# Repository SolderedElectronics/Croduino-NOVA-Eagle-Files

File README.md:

# Croduino NOVA Open Source Hardware Files

Buy Croduino NOVA [here](https://e-radionica.com/en/croduino-nova.html).

## Description and details
Croduino NOVA is microcontroller board capable of connecting to WiFi Internet network, made in Croatia(EU). It is based on very popular ESP8266 which is struggle to use standalone. With NOVA, just plug the board into USB port and start programming your next Internet-connected project(IoT)! Besides that, the board fits perfectly into a breadboard so prototyping is even more simple. Connecting the physical world to internet was never easier.

The braing of NOVA is ESP8266 produced by Espressif. It comes with complete WiFi(client and server side) and integrated TCP/IP stack which supports DNS. The most important thing - it is programmable from Arduino, there is even no need to manually reset the board due to auto-reset circuit onboard. It works at 80MHz frequency, has 1MB of flash for your code(of which 0.8MB available to you) and 82kB of RAM memory(of which 49kB available to you). NOVA also supports I2C, SPI and serial communication, there is 9 GPIO for you of which all support PWM and 1 analog input. Additionally, there is onboard: CP2102 USB to UART bridge (used for USB communication), 3.3V voltage regulator, 4 LEDs, it has FCC and CE certificate etc. In detail:

- ESP8266 in ESP-12 package
- 80MHz, 1MB flash, 82kB RAM
- programmable from Arduina!
- 9 GPIO pins of which all support PWM
- 1 analog input(ADC), max. voltage 1V i 5V
- I2C, SPI, serial communication
- CP2102 USB to UART bridge with micro USB connector
- 3.3V voltage regulator
- LEDs: power, tx, rx, GPIO13
- automatical hardware reset before upload of code
- two pushbuttons: reset i GPIO0
- comes with micro USB cable
- FCC i CE certificates for ESP-12

ESP8266 on-board is loaded with default bootloader.

## Repository content
This repo contains Cadsoft Eagle .sch and .brd files for the board. It also contains schematic in .pdf created from .sch Eagle file. 
Files have been arranged into folders for navigating between different versions of board. 
Tip: layer 200 shows top silkscreen and layer 208 is the bottom silkscreen. tParts and bParts layers are not used.

## Docs
- [Croduino NOVA product page](https://e-radionica.com/en/croduino-nova.html)

## Board versions
- v1.0 - inital published version 
- v1.1 - there was error near GPIO1 pushbutton in which GPIO0 was always directly connected to gnd. Fixed now. Silkscreen text is also a bit bigger and more readable.
- v1.2 - slight redesign, board longer 5mm and wider 2.54mm, added battery charger, changed LDO, parts rearranged. 

## License info
This product is [Open Source Hardware](https://en.wikipedia.org/wiki/Open-source_hardware), yay! Feel free to use it for any purpose you wish, but if you are ever in [Osijek, Croatia](https://goo.gl/maps/tEC2jWnBXJQpk9RJ7), you owe us a beer.

For any tech questions, please write on our [forum](http://forum.e-radionica.com/en/). If you find an Issue, please open one at GitHub. If you can improve our product, fork us.

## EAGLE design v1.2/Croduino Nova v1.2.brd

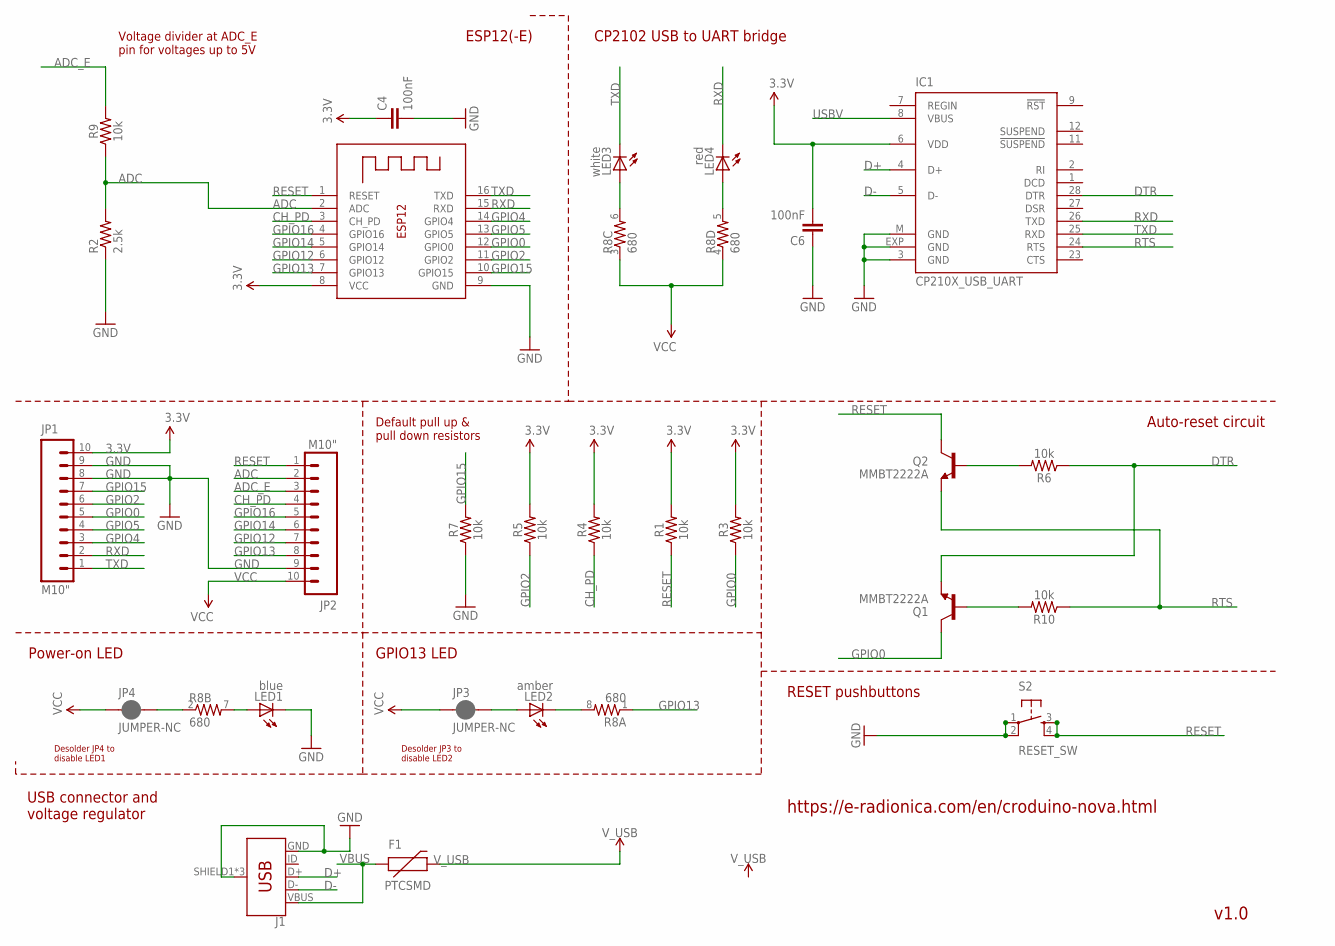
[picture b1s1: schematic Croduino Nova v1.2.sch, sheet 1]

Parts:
C4, C6: 100nF; 0603-CAP
F1: PTCSMD; PTC-1206
IC1: CP210X_USB_UART; MLP28
J1: USB_MICRO-BREDUCED_PASTE; USB-B-MICRO-SMD_RED_PASTE
JP1, JP2: M10"; 1X10
JP3, JP4: JUMPER-NC; SMT-JUMPER_2_NC_PASTE_NO-SILK
LED1: blue; CHIP-LED0805
LED2: amber; CHIP-LED0805
LED3: white; CHIP-LED0805
LED4: red; CHIP-LED0805
Q1, Q2: MMBT2222A; SOT23-3
R1, R3, R4, R5, R6, R7, R9, R10: 10k; 0603
R2: 2.5k; 0603-RES
R8: 680; 0603-ARV
S2: RESET_SW; TACTILE_SWITCH_SMD
X1: ESP8266-12; ESP-12

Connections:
3.3V: C4.1, C6.2, IC1.6 (VDD), JP1.10, R1.2, R3.2, R4.2, R5.2, X1.8 (VCC); also elsewhere on the board
ADC: JP2.2, R2.2, R9.1, X1.2 (ADC)
ADC_E: JP2.3, R9.2
CH_PD: JP2.4, R4.1, X1.3 (CH_PD)
D+: IC1.4 (D+), J1.D+
D-: IC1.5 (D-), J1.D-
DTR: IC1.28 (DTR), Q1.2 (E), R6.1
GND: C4.2, C6.1, IC1.3 (GND), IC1.EXP (GND), IC1.M (GND), J1.GND, J1.SHIELD1 (SHIELD), J1.SHIELD2 (SHIELD), J1.SHIELD3 (SHIELD), JP1.8, JP1.9, JP2.9, LED1.C, R2.1, R7.1, S2.1, S2.2, X1.9 (GND); also elsewhere on the board
GPIO0: JP1.5, Q1.3 (C), R3.1, X1.12 (GPIO0)
GPIO2: JP1.6, R5.1, X1.11 (GPIO2)
GPIO4: JP1.3, X1.14 (GPIO4)
GPIO5: JP1.4, X1.13 (GPIO5)
GPIO12: JP2.7, X1.6 (GPIO12)
GPIO13: JP2.8, R8.1, X1.7 (GPIO13)
GPIO14: JP2.6, X1.5 (GPIO14)
GPIO15: JP1.7, R7.2, X1.10 (GPIO15)
GPIO16: JP2.5, X1.4 (GPIO16)
unnamed: LED3.A, R8.6 (2)
unnamed: JP4.2, R8.2 (1)
unnamed: LED1.A, R8.7 (2)
unnamed: LED4.A, R8.5 (2)
unnamed: LED2.C, R8.8 (2)
unnamed: JP3.2, LED2.A
unnamed: Q1.1 (B), R10.2
unnamed: Q2.1 (B), R6.2
RESET: JP2.1, Q2.3 (C), R1.1, S2.3, S2.4, X1.1 (RESET)
RTS: IC1.24 (RTS), Q2.2 (E), R10.1
RXD: IC1.26 (TXD), JP1.2, LED4.C, X1.15 (RXD)
TXD: IC1.25 (RXD), JP1.1, LED3.C, X1.16 (TXD)
USBV: IC1.8 (VBUS)
VBUS: F1.1, J1.VBUS
VCC: JP2.10, JP3.1, JP4.1, R8.3 (1), R8.4 (1); also elsewhere on the board
V_USB: F1.2; also elsewhere on the board

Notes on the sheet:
USB connector and voltage regulator
Power-on LED
GPIO13 LED
Desolder JP4 to disable LED1
Desolder JP3 to disable LED2
ESP12(-E)
CP2102 USB to UART bridge
Voltage divider at ADC_E pin for voltages up to 5V
Default pull up & pull down resistors
Auto-reset circuit
RESET pushbuttons
https://e-radionica.com/en/croduino-nova.html
v1.0

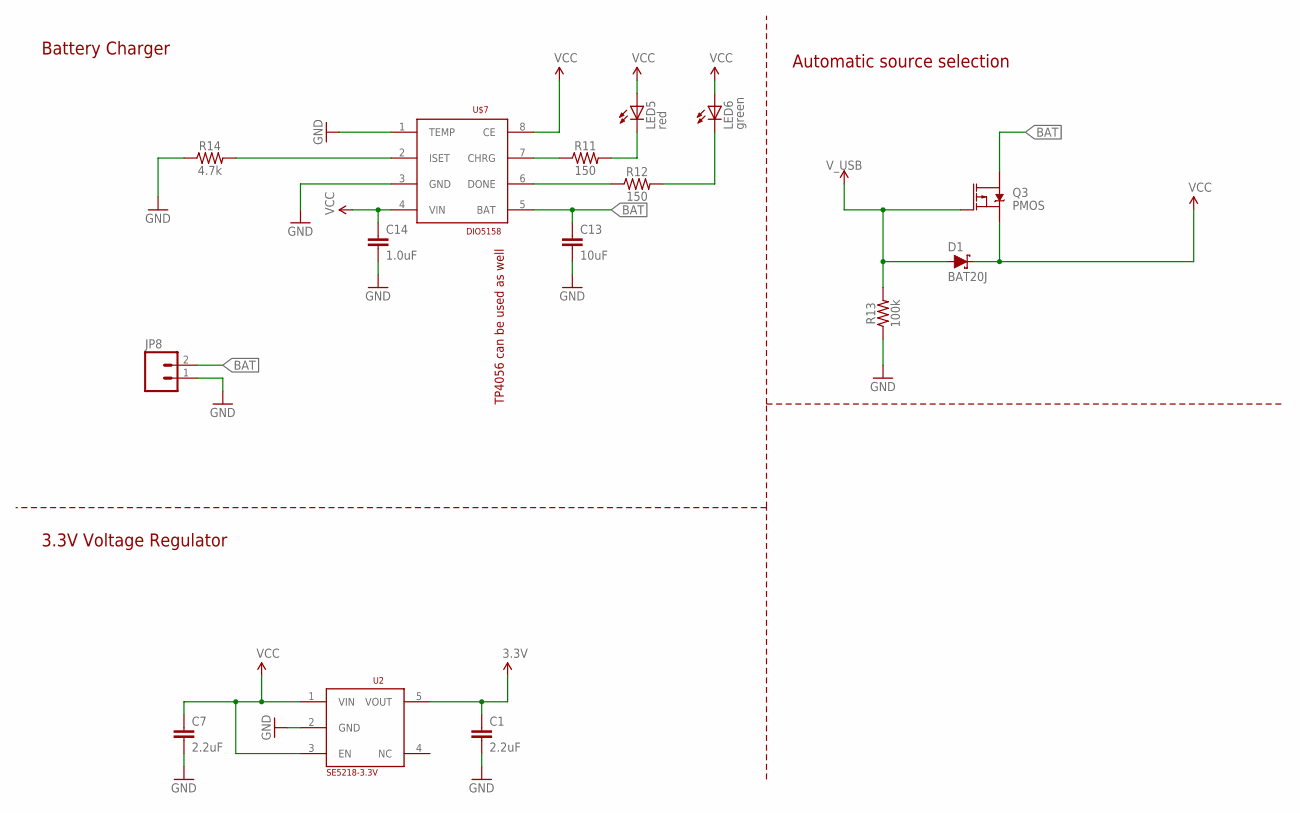
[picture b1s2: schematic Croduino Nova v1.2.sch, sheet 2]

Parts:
C1, C7: 2.2uF; 0603
C13: 10uF; 1206
C14: 1.0uF; 0603
D1: BAT20J; SOD-323
JP8: M02-JST-2MM-SMT; JST-2-SMD
LED5: red; CHIP-LED0805
LED6: green; CHIP-LED0805
Q3: PMOS; SOT23-3
R11, R12: 150; 0603
R13: 100k; 0603
R14: 4.7k; 0603
U2: SE5218-3.3V; SOT23-5
U$7: DIO5158; SOIC-8

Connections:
3.3V: C1.1, U2.5 (VOUT); also elsewhere on the board
BAT: C13.1, JP8.2, Q3.3 (D), U$7.5 (BAT)
CHRG: R11.1, U$7.7 (CHRG)
DONE: R12.1, U$7.6 (DONE)
GND: C1.2, C7.2, C13.2, C14.2, JP8.1, R13.1, R14.1, U2.2 (GND), U$7.1 (TEMP), U$7.3 (GND); also elsewhere on the board
ISET: R14.2, U$7.2 (ISET)
LED1: LED5.C, R11.2
LED2: LED6.C, R12.2
VCC: C7.1, C14.1, D1.C, LED5.A, LED6.A, Q3.2 (S), U2.1 (VIN), U2.3 (EN), U$7.4 (VIN), U$7.8 (CE); also elsewhere on the board
V_USB: D1.A, Q3.1 (G), R13.2; also elsewhere on the board

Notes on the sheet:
TP4056 can be used as well
3.3V Voltage Regulator
Battery Charger
Automatic source selection

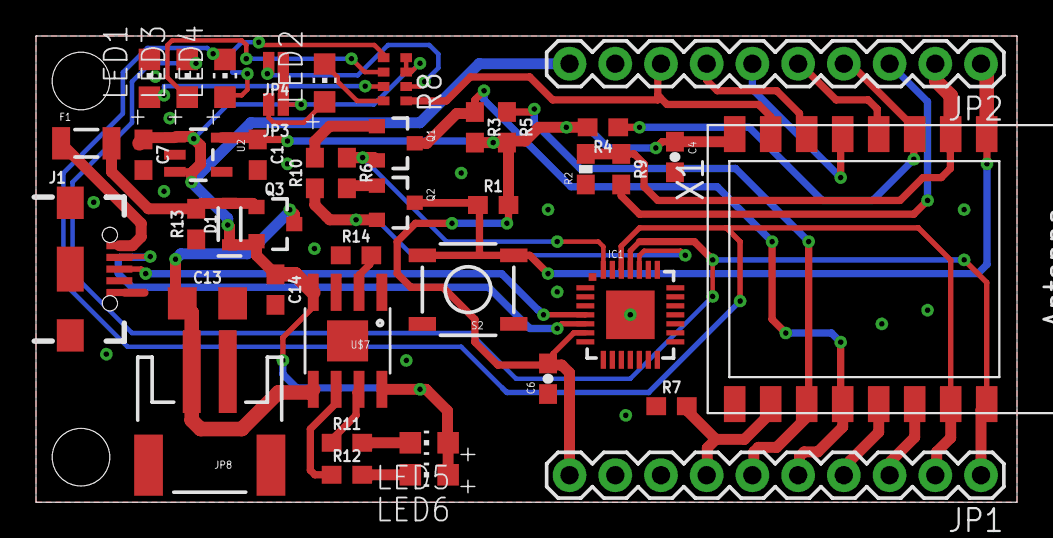
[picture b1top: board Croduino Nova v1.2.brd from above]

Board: 2 copper layers, 54.5 x 25.9 mm, 48 parts (0 on the bottom side), 38 nets.

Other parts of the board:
U$1: LOGO-3MM
U$2: CRODUINO_NOVA
U$3: OSH-3MM
U$4: E-R.IO-6MM
U$5: MADE-IN-CROATIA-10MM
U$6: E-R.IO-BACK-6MM

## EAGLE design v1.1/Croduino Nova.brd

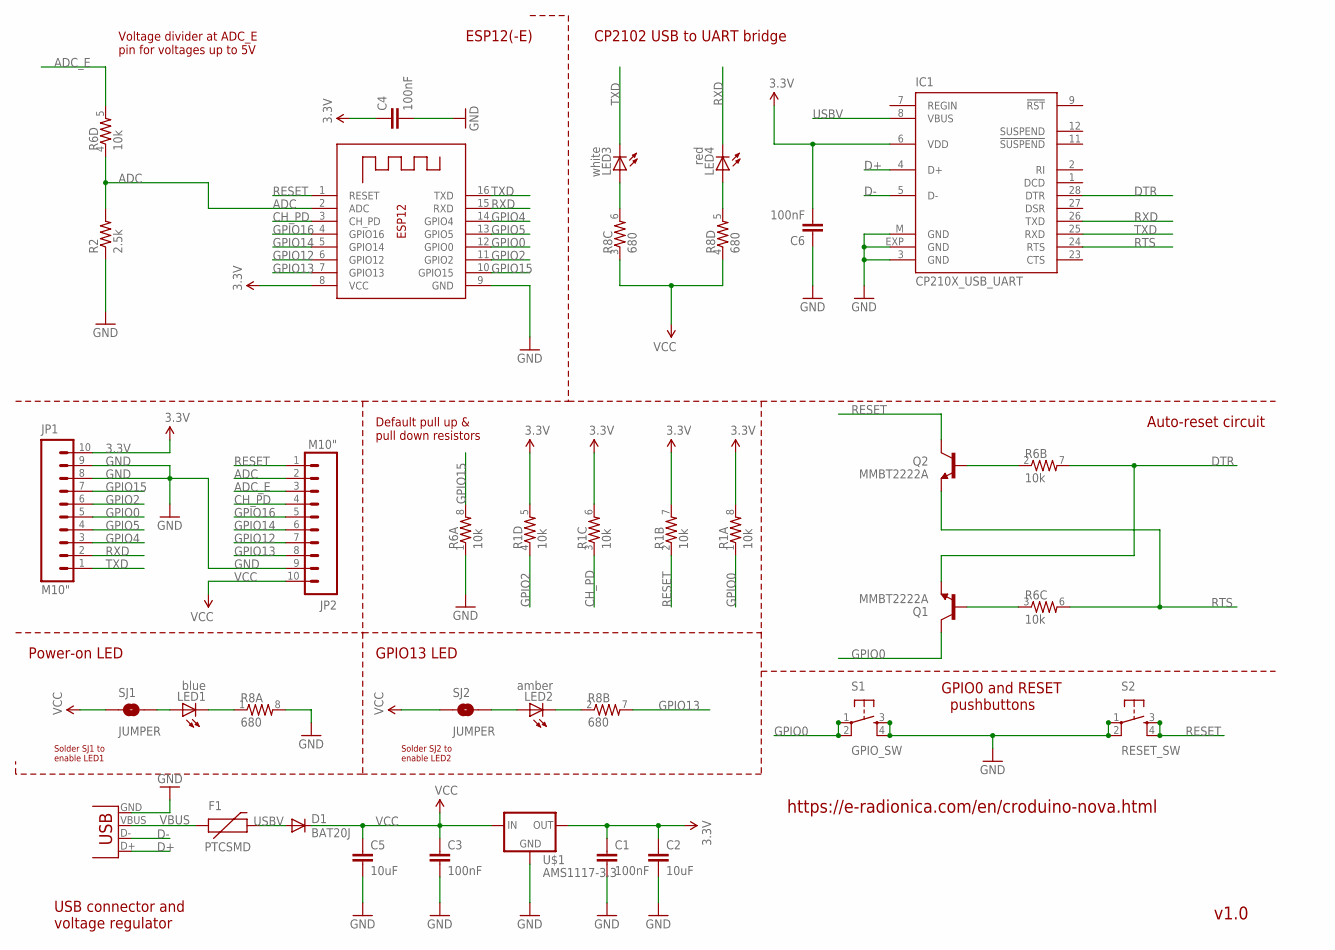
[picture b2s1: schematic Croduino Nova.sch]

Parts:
C1, C3, C4, C6: 100nF; 0603-CAP
C2, C5: 10uF; 1206
D1: BAT20J; SOD-323
F1: PTCSMD; PTC-1206
IC1: CP210X_USB_UART; MLP28
JP1, JP2: M10"; 1X10
LED1: blue; CHIP-LED0805
LED2: amber; CHIP-LED0805
LED3: white; CHIP-LED0805
LED4: red; CHIP-LED0805
Q1, Q2: MMBT2222A; SOT23-3
R1, R6: 10k; 0603-ARV
R2: 2.5k; 0603-RES
R8: 680; 0603-ARV
S1: GPIO_SW; TACTILE_SWITCH_SMD
S2: RESET_SW; TACTILE_SWITCH_SMD
SJ1, SJ2: JUMPER; SJ_2S
U$1: AMS1117-3.3; SOT223
X1: ESP8266-12; ESP-12
X2: USB-MICROB

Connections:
3.3V: C1.1, C2.1, C4.1, C6.2, IC1.6 (VDD), JP1.10, R1.5 (2), R1.6 (2), R1.7 (2), R1.8 (2), U$1.4 (OUT), X1.8 (VCC)
ADC: JP2.2, R2.2, R6.4 (1), X1.2 (ADC)
ADC_E: JP2.3, R6.5 (2)
CH_PD: JP2.4, R1.3 (1), X1.3 (CH_PD)
D+: IC1.4 (D+), X2.D+
D-: IC1.5 (D-), X2.D-
DTR: IC1.28 (DTR), Q1.2 (E), R6.7 (2)
GND: C1.2, C2.2, C3.2, C4.2, C5.2, C6.1, IC1.3 (GND), IC1.EXP (GND), IC1.M (GND), JP1.8, JP1.9, JP2.9, R2.1, R6.1, R8.8 (2), S1.3, S1.4, S2.1, S2.2, U$1.1 (ADJ), X1.9 (GND), X2.GND
GPIO0: JP1.5, Q1.3 (C), R1.1, S1.1, S1.2, X1.12 (GPIO0)
GPIO2: JP1.6, R1.4 (1), X1.11 (GPIO2)
GPIO4: JP1.3, X1.14 (GPIO4)
GPIO5: JP1.4, X1.13 (GPIO5)
GPIO12: JP2.7, X1.6 (GPIO12)
GPIO13: JP2.8, R8.7 (2), X1.7 (GPIO13)
GPIO14: JP2.6, X1.5 (GPIO14)
GPIO15: JP1.7, R6.8 (2), X1.10 (GPIO15)
GPIO16: JP2.5, X1.4 (GPIO16)
unnamed: LED3.A, R8.6 (2)
unnamed: LED1.A, SJ1.2
unnamed: LED1.C, R8.1
unnamed: LED4.A, R8.5 (2)
unnamed: LED2.A, SJ2.2
unnamed: LED2.C, R8.2 (1)
unnamed: Q1.1 (B), R6.3 (1)
unnamed: Q2.1 (B), R6.2 (1)
RESET: JP2.1, Q2.3 (C), R1.2 (1), S2.3, S2.4, X1.1 (RESET)
RTS: IC1.24 (RTS), Q2.2 (E), R6.6 (2)
RXD: IC1.26 (TXD), JP1.2, LED4.C, X1.15 (RXD)
TXD: IC1.25 (RXD), JP1.1, LED3.C, X1.16 (TXD)
USBV: D1.2 (A), F1.2, IC1.8 (VBUS)
VBUS: F1.1, X2.VBUS
VCC: C3.1, C5.1, D1.1 (C), JP2.10, R8.3 (1), R8.4 (1), SJ1.1, SJ2.1, U$1.3 (IN)

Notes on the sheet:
USB connector and voltage regulator
Power-on LED
GPIO13 LED
Solder SJ1 to enable LED1
Solder SJ2 to enable LED2
ESP12(-E)
CP2102 USB to UART bridge
Voltage divider at ADC_E pin for voltages up to 5V
Default pull up & pull down resistors
Auto-reset circuit
GPIO0 and RESET pushbuttons
https://e-radionica.com/en/croduino-nova.html
v1.0

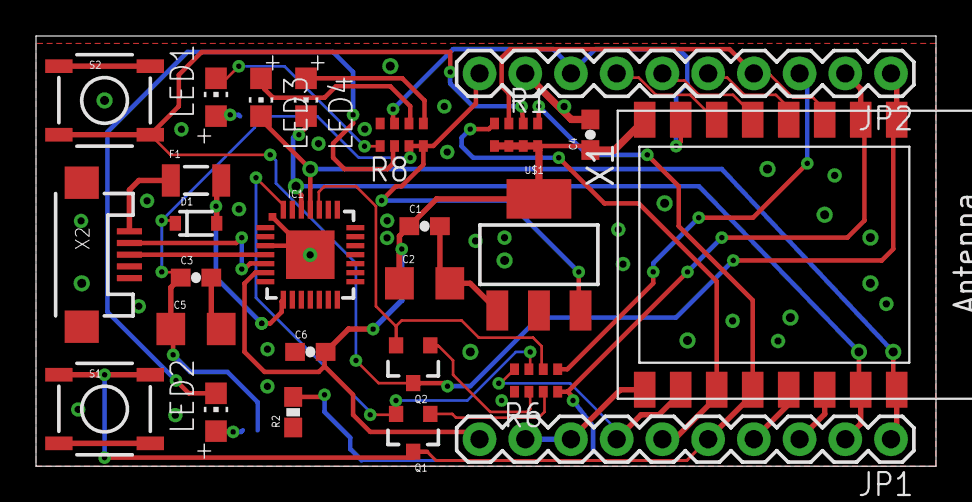
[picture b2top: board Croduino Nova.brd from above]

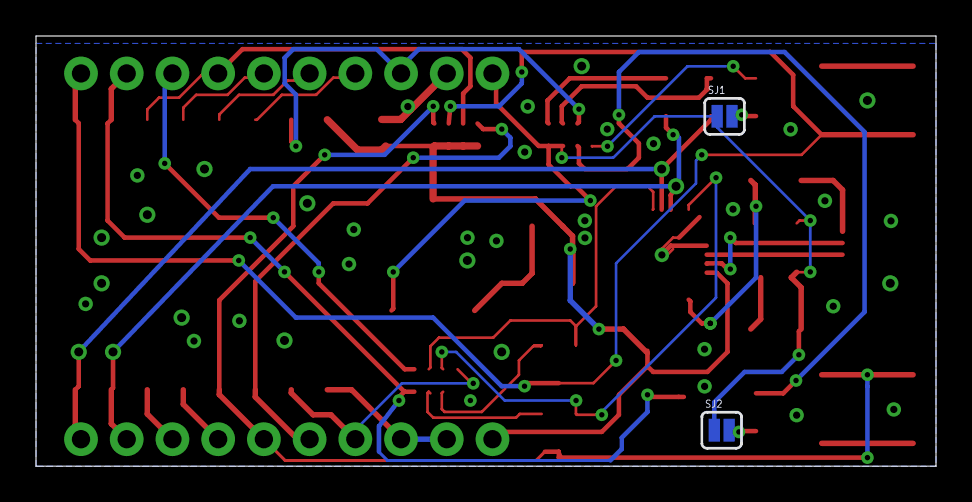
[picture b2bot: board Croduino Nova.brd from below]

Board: 2 copper layers, 50.0 x 23.9 mm, 31 parts (2 on the bottom side), 32 nets.

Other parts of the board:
U$2: CRODUINO_NOVA
U$3: NOVI_LOGO-4MM
U$4: OSH3MM

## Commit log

2016-02-12 Inital upload of files
2016-08-17 Added v1.1
    v1.1 of Eagle files was added. There small change in PCB design.
2017-10-19 Added v1.2 version of the board
2018-08-10 added v1.2 version
2018-11-26 README update

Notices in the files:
parts and their libraries:
SparkFun: Licensing: CC v3.0 Share-Alike You are welcome to use this library for commercial purposes.
SparkFun-Resistors: Licensing: Creative Commons ShareAlike 4.0 International - https://creativecommons.org/licenses/by-sa/4.0
